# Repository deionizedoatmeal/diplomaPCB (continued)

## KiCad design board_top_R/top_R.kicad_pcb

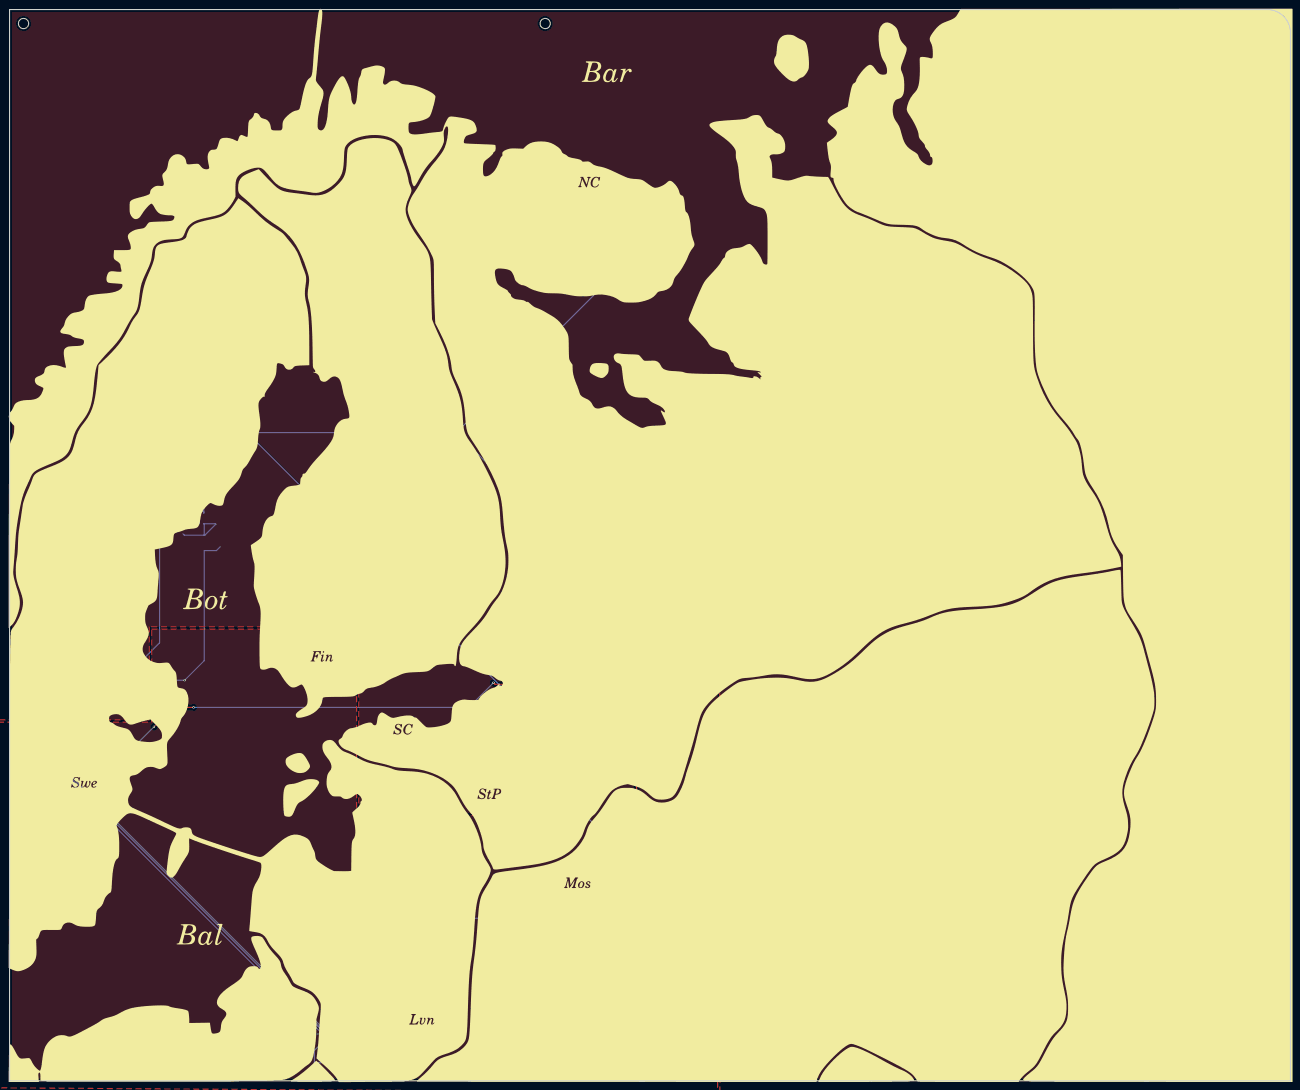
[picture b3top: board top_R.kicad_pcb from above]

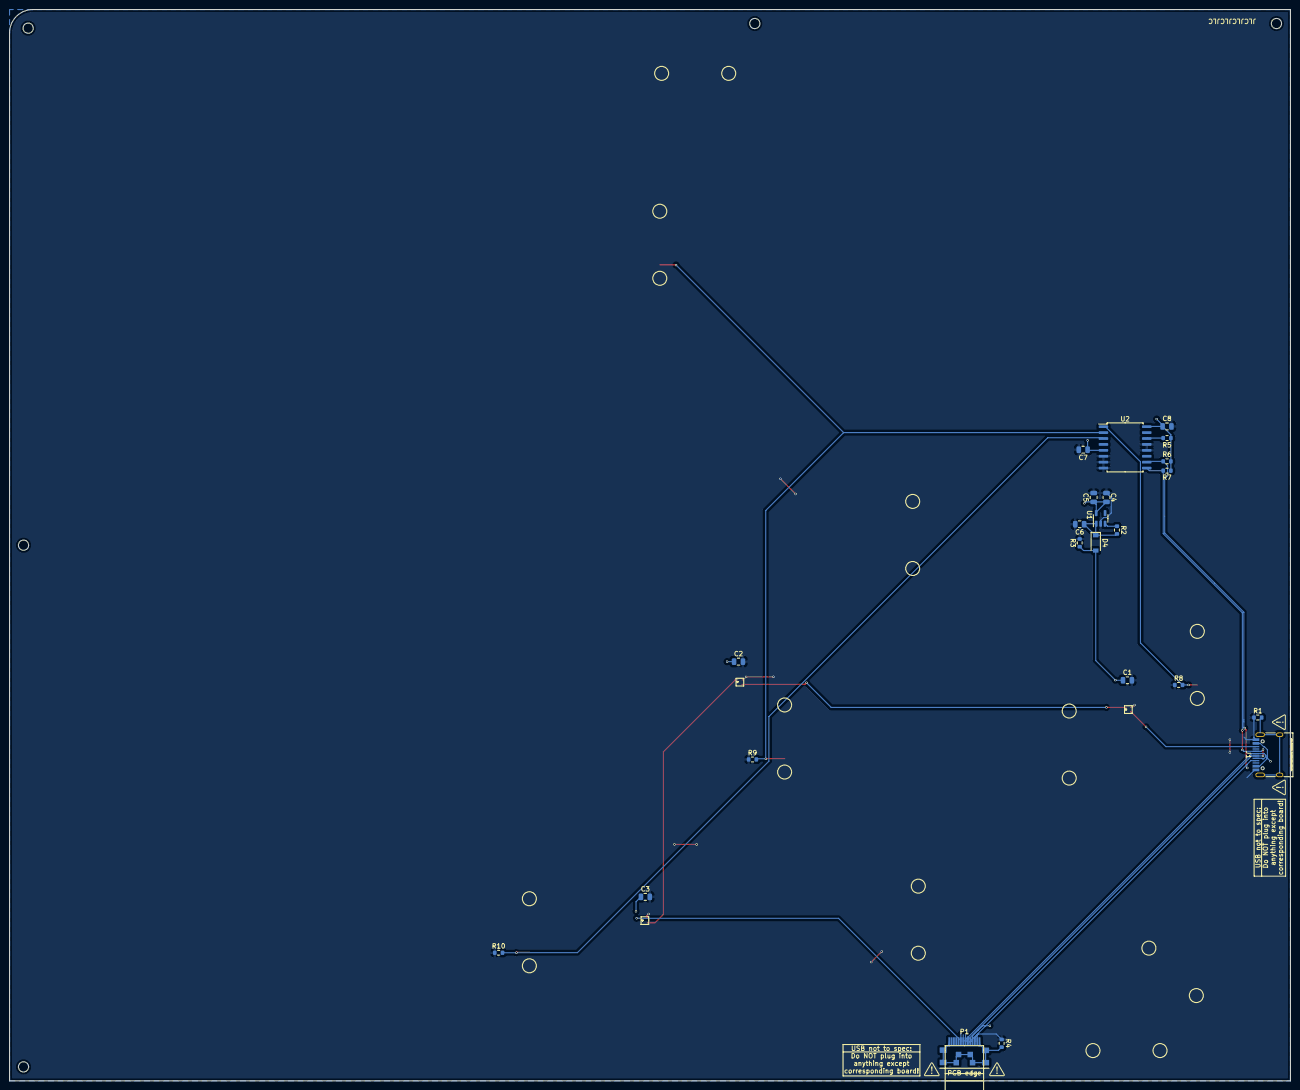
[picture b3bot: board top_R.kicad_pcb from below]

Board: 2 copper layers, 275.0 x 230.0 mm, 39 parts (23 on the bottom side), 18 nets.

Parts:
C1, C2, C3: 0.1µ; C_0805_2012Metric
C4, C5, C6: 10µ; C_0805_2012Metric
C7: 0.1u; C_0805_2012Metric
C8: 10u; C_0805_2012Metric
D1, D2, D3: SK6805-EC
D4: MBR0540; D_SOD-123
H1, H2, H3, H4, H5: MountingHole; MountingHole_2.2mm_M2
J1: USB_C_Receptacle_USB2.0; USB_C_Receptacle_HRO_TYPE-C-31-M-12
P1: USB_C_Plug; USB_C_Plug_edge_launch
R1, R4: 1M; R_0603_1608Metric
R2, R3, R6, R7, R8, R9, R10: 10k; R_0603_1608Metric
R5: 1k; R_0603_1608Metric
TP1, TP2, TP3, TP4, TP5, TP6, TP7, TP8: TestPoint; TestPoint_Pad_D2.0mm
U1: AP2112K-3.3; SOT-23-5
U2: PCF8591; SOIC-16W_7.5x10.3mm_P1.27mm

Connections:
+3V3: C4.1, C5.1, C7.1, C8.1, R5.2, R6.1, R7.1, TP1.1, TP3.1, TP4.1, TP5.1, U1.5 (VOUT), U2.5 (A0), U2.16 (VDD)
+5V: C1.1, C2.1, C3.1, D1.2 (VDD), D2.2 (VDD), D3.2 (VDD), D4.2 (A), J1.A4 (VBUS), J1.A9 (VBUS), J1.B4 (VBUS), J1.B9 (VBUS), P1.A4 (VBUS), P1.B9 (VBUS), R3.1
/GPIO0_SDA: J1.A6 (D+), J1.B6 (D+), P1.A6 (D+), R7.2, U2.9 (SDA)
/GPIO1_SCL: J1.A5 (CC1), P1.A5 (CC), R6.2, U2.10 (SCL)
/LED_TL2TR: D1.1 (DIN), J1.B5 (CC2)
/LED_TR2BR: D3.3 (DOUT), P1.B5 (VCONN)
/SUP7: R8.2, TP6.1, U2.1 (AIN0)
/SUP8: R9.2, TP2.1, TP7.1, U2.2 (AIN1)
/SUP9: R10.2, TP8.1, U2.3 (AIN2)
/SUP34: J1.A7 (D-), J1.B7 (D-), P1.A7 (D-)
GND: C1.2, C2.2, C3.2, C4.2, C5.2, C6.2, C7.2, C8.2, D1.4 (VSS), D2.4 (VSS), D3.4 (VSS), J1.A1 (GND), J1.A12 (GND), J1.B1 (GND), J1.B12 (GND), P1.A1 (GND), P1.B12 (GND), R1.1, R3.2, R4.1, R8.1, R9.1, R10.1, U1.2 (GND), U2.6 (A1), U2.7 (A2), U2.8 (VSS), U2.12 (EXT), U2.13 (AGND)
unnamed: D1.3 (DOUT), D2.1 (DIN)
unnamed: D2.3 (DOUT), D3.1 (DIN)
unnamed: J1.S1 (SHIELD), R1.2
unnamed: P1.S1 (SHIELD), R4.2
unnamed: R2.1, U1.3 (EN)
unnamed: R5.1, U2.14 (VREF)
VS: C6.1, D4.1 (K), R2.2, U1.1 (VIN)

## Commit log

2022-05-28 inital
2022-05-28 inital code commit
2022-05-28 combined all boards into one kicad PCB to render together
2022-05-28 added BoM
2022-05-28 edit BoM
2022-05-28 readme edits
2022-05-29 added some cutouts from another project to the stencil
2022-05-29 readme
2022-05-29 readme fix
